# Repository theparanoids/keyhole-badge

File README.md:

# Paranoids DEFCON Badge
> PCB design and firmware for a badge given out at DEFCON 2022

## Table of Contents

- [Background](#background)
- [Install](#install)
- [Usage](#usage)
- [Contribute](#contribute)
- [License](#license)

## Background

The Paranoids have designed a sound-reactive LED electronic conference badge for DEFCON 2022. This repository contains the PCB design files for the badge and the source code to the firmware that runs on the microcontroller.

This badge is designed around a Nordic [nRF52833](https://www.nordicsemi.com/Products/nRF52833) SoC embedded in a Laird [BL653](https://www.lairdconnect.com/wireless-modules/bluetooth-modules/bluetooth-5-modules/bl653-series-bluetooth-51-802154-nfc-module) module. The badge features wireless connectivity (Bluetooth Low Energy in this firmware implementation), a NFC coil, a microphone, buttons, and LEDs.

The firmware is built using the [nRF Connect SDK](https://www.nordicsemi.com/Products/Development-software/nRF-Connect-SDK) and [Zephyr RTOS](https://zephyrproject.org/). It advertises BLE beacons and listens for beacons coming from neighboring badges, lighting up the LEDs according to the number of badges detected. It also blinks the LEDs either in response to sound or in other patterns, which are unlocked by inputting secret codes using the buttons.

## Install

In order to edit the PCB design files, you will need to install [Kicad](https://www.kicad.org/) version 6 or above. The badge design is located in the `eda/` subdirectory. A pogo pin jig used during manufacturing is located in the `jig/` subdirectory. Opening the `.kicad_pro` project file should automatically load both the schematic and PCB design.

If you only want to view the schematic or the final board layout, PDFs of the final version are located in [final-artefacts](final-artefacts).

In order to compile the firmware, you will need to install the [Nordic nRF Connect SDK](https://www.nordicsemi.com/Products/Development-software/nrf-connect-sdk) v1.9.0. This can be installed according to the official instructions. If you are using nRF Connect for Desktop and the Toolchain Manager, select "Open Terminal" from the arrow dropdown after installing the SDK. From this terminal, the firmware can be built using the following command:

```bash
cd fw/
west build
```

The output will be located in `fw/build/zephyr/zephyr.elf`.

There are miscellaneous scripts written in Python that were used during testing and development. These require Python3, pySerial, NumPy, and scikit-image. These can be installed via pip using the following commands:

```bash
# Create a new Python virtual environment
python3 -m venv venv
# Activate the virtual environment
source venv/bin/activate
# Install libraries
pip install pyserial numpy scikit-image
```

LED positions were computed using [SolveSpace](https://solvespace.com/). This is saved in the [notes.slvs](eda/notes.slvs) file.

## Usage

The Paranoids badge does not contain any kind of bootloader or firmware update functionality, so installing new firmware requires connecting to SWD (Serial Wire Debug) test pads on the back of the badge. This can be done either with a temporary jig or by soldering wires or pin headers. The test points are labeled on the [backside fabrication drawing](final-artefacts/badge/pdf/badge_eda-B_Fab.pdf). Connections that are required are as follows:

* `TP3 / +V` -- Microcontroller supply voltage. This may be labeled as "VCC" or "Vtarget" or similar. Corresponds to pin 1 of the ARM 10-pin connector. **Caution**: This pin is intended to be used as a voltage reference and not as a means to power the badge. Although powering the badge from this test point does work, doing so will bypass the reverse polarity protection circuitry. There is also no protection against back-powering the battery, which can result in a dangerous condition. If power is supplied using this test point, ensure that connections are correct and that batteries are not installed. Nominal voltage 3 V.
* `TP9 / GND` -- Ground reference. Corresponds to pins 3/5/9 of the ARM 10-pin connector.
* `TP5 / SWDCLK` -- SWD clock pin. Corresponds to pin 4 of the ARM 10-pin connector.
* `TP6 / SWDIO` -- SWD data pin. Corresponds to pin 2 of the ARM 10-pin connector.
* `TP4 / ~RST` (optional) -- reset pin (active low). Corresponds to pin 10 of the ARM 10-pin connector. Not required in most cases as reset can be triggered over SWD.
* `TP7 / DBGTX` (optional) -- debug serial port, output from the board. In this firmware, this is configured with a 115200 baud 8n1 serial port for printing debug messages.
* `TP8 / DBGRX` (optional) -- debug serial port, input into the board. In this firmware, this is technically configured as part of the debug console, but input is never read.

All signals are referenced to the voltage on `TP3`.

Programming new firmware requires an external ARM SWD debug probe, such as a [Black Magic Probe](https://1bitsquared.com/products/black-magic-probe) or a [J-Link](https://www.segger.com/products/debug-probes/j-link/). It is also possible to [use a Raspberry Pi](https://learn.adafruit.com/programming-microcontrollers-using-openocd-on-raspberry-pi) or any other compatible debug adapter.

Example commands for programming using a Black Magic Probe:

```
$ arm-none-eabi-gdb build/zephyr/zephyr.elf
(gdb) target extended-remote /dev/cu.usbmodemXXXXXXXX
(gdb) monitor swdp_scan
(gdb) attach 1
(gdb) load
```

### Firmware debugging features

The badge connects the USB pins of the nRF52 chip to a USB micro-B connector on the bottom of the board. In this firmware, this is configured as a CDC-ACM serial port featuring a debug console (different from the one on the test points). Typing `help` will show a list of debug commands.

This USB debug console allows for capturing sound onto a connected computer. To capture sound, send the command `debug sound on`. The badge will then continuously output a stream of audio samples in signed 16-bit little endian format at 16 kHz with no framing. The [test_sound.py](fw/src/test_sound.py) script demonstrates capturing approximately 10 seconds of audio via this mechanism and writing it to a raw file which can be opened in tools such as [Audacity](https://www.audacityteam.org/).

If the flash memory of the nRF52 is blank, the firmware will start in factory test mode. Completion of factory testing is stored in flash memory, so none of the badges given out at DEFCON will start in test mode. As long as the Zephyr NVS data at the end of flash memory is not erased when programming new firmware, the badge will not enter test mode again. Test mode can be either re-entered after completion or forcefully bypassed without completing it by using the USB debug console. The factory test procedure goes through the following phases:

1. Both eyes should be red. The edge LEDs should have a pattern of three lit LEDs animating and moving around in a loop. The other LEDs on the edge should be off. One LED should be blue, the next should be green, and the final lit LED should be red. The primary purpose of this test phase is to ensure that there are no breaks in the LED chain. To proceed to the next phase, press button SW1.
2. Both eyes should be green. One LED on the edge, immediately below the eyes, should be white. All other LEDs on the edge should be off. To proceed to the next phase, press button SW2.
3. Both eyes should be blue. Two LEDs on the edge, immediately below the eyes, should be white. All other LEDs on the edge should be off. To proceed to the next phase, press button SW3.
4. Both eyes should be white. Three LEDs on the edge, immediately below the eyes, should be white. All other LEDs on the edge should be off. To proceed to the next phase, press button SW4.
5. Both eyes should be white. All LEDs on the edge should be white. At this point in the test procedure, the edge LEDs, all three primary colors of the eye LEDs, and all buttons will have been tested. This phase with all LEDs lit also serves as a brief test of maximum current draw in order to try to catch obvious issues with the 5 V SMPS. To proceed to the next phase (finishing and exiting test mode), play a 440 Hz tone. This tests the microphone.

## Contribute

Please refer to [the contributing.md file](Contributing.md) for information about how to get involved.

## Maintainers
- R: rou@yahooinc.com

## License
- This project is licensed under the terms of the [Apache 2.0](LICENSE-Apache-2.0) open source license. Please refer to [LICENSE](LICENSE) for the full terms.

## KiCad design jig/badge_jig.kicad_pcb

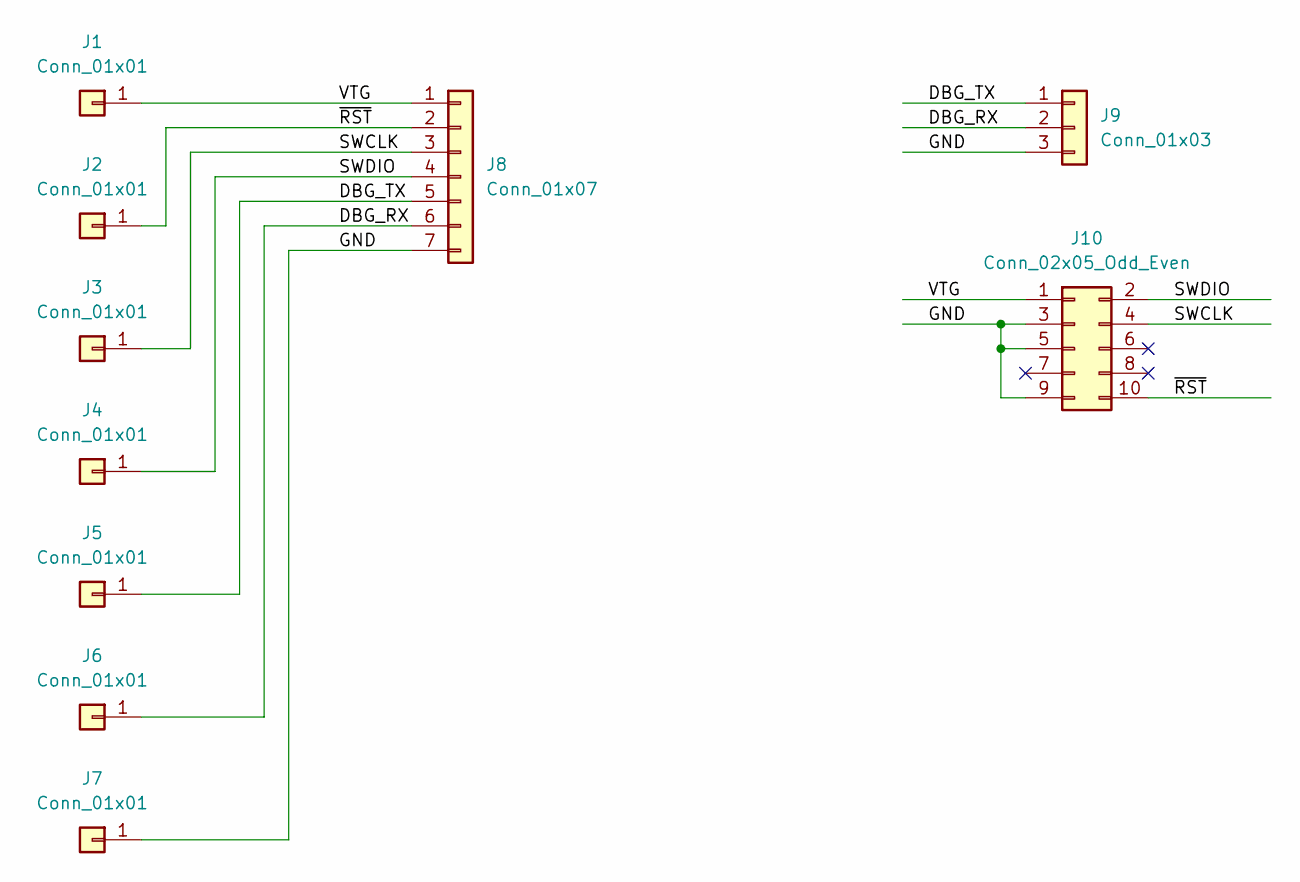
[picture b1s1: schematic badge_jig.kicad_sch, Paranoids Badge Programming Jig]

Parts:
J1, J2, J3, J4, J5, J6, J7: Conn_01x01; pogopin
J8: Conn_01x07; PinHeader_1x07_P2.54mm_Horizontal
J9: Conn_01x03; PinHeader_1x03_P2.54mm_Horizontal
J10: Conn_02x05_Odd_Even; PinHeader_2x05_P2.54mm_Vertical

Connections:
/DBG_RX: J6.1, J8.6, J9.2
/DBG_TX: J5.1, J8.5, J9.1
/GND: J7.1, J8.7, J9.3, J10.3, J10.5, J10.9
/SWCLK: J3.1, J8.3, J10.4
/SWDIO: J4.1, J8.4, J10.2
/VTG: J1.1, J8.1, J10.1
/~RST: J2.1, J8.2, J10.10

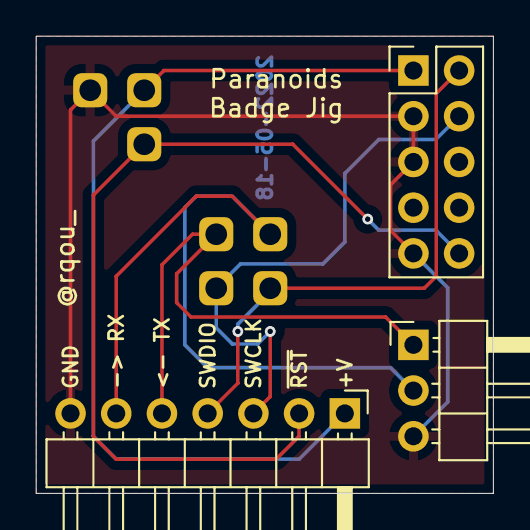
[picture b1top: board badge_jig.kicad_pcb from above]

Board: 2 copper layers, 25.4 x 25.4 mm, 10 parts (0 on the bottom side), 7 nets.

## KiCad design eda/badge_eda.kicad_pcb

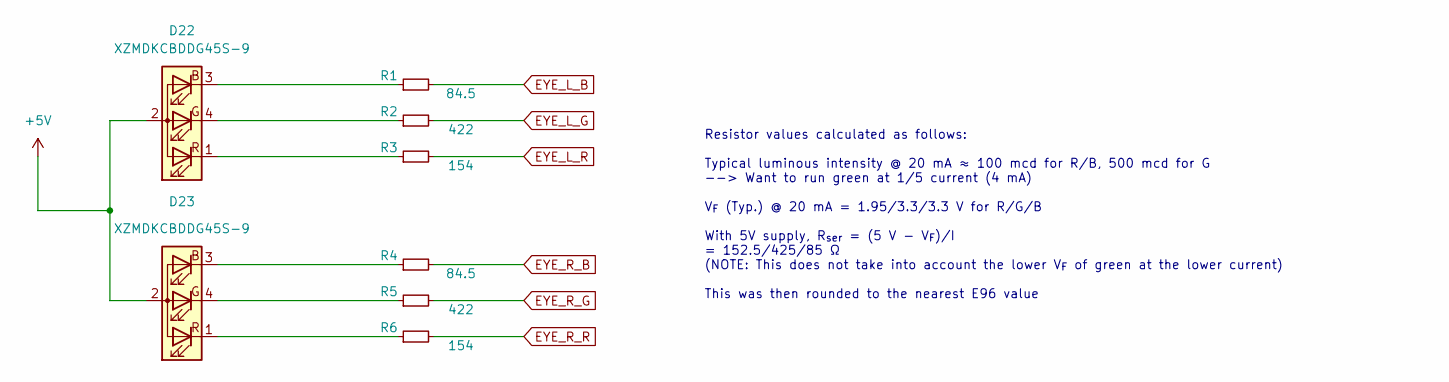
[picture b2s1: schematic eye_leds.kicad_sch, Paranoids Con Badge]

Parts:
D22, D23: XZMDKCBDDG45S-9; LED_SunLed-PLCC4_3.2x2.8mm_CW
R1, R4: 84.5; R_0603_1608Metric
R2, R5: 422; R_0603_1608Metric
R3, R6: 154; R_0603_1608Metric

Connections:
+5V: D22.2 (A), D23.2 (A); also elsewhere on the board
EYE_L_B: R1.2; also elsewhere on the board
EYE_L_G: R2.2; also elsewhere on the board
EYE_L_R: R3.2; also elsewhere on the board
EYE_R_B: R4.2; also elsewhere on the board
EYE_R_G: R5.2; also elsewhere on the board
EYE_R_R: R6.2; also elsewhere on the board
unnamed: D22.1 (RK), R3.1
unnamed: D22.3 (BK), R1.1
unnamed: D22.4 (GK), R2.1
unnamed: D23.1 (RK), R6.1
unnamed: D23.3 (BK), R4.1
unnamed: D23.4 (GK), R5.1

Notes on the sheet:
Resistor values calculated as follows: Typical luminous intensity @ 20 mA ≈ 100 mcd for R/B, 500 mcd for G --> Want to run green at 1/5 current (4 mA) V_{F} (Typ.) @ 20 mA = 1.95/3.3/3.3 V for R/G/B With 5V supply, R_{ser} = (5 V - V_{F})/I = 152.5/425/85 Ω (NOTE: This does not take into account th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

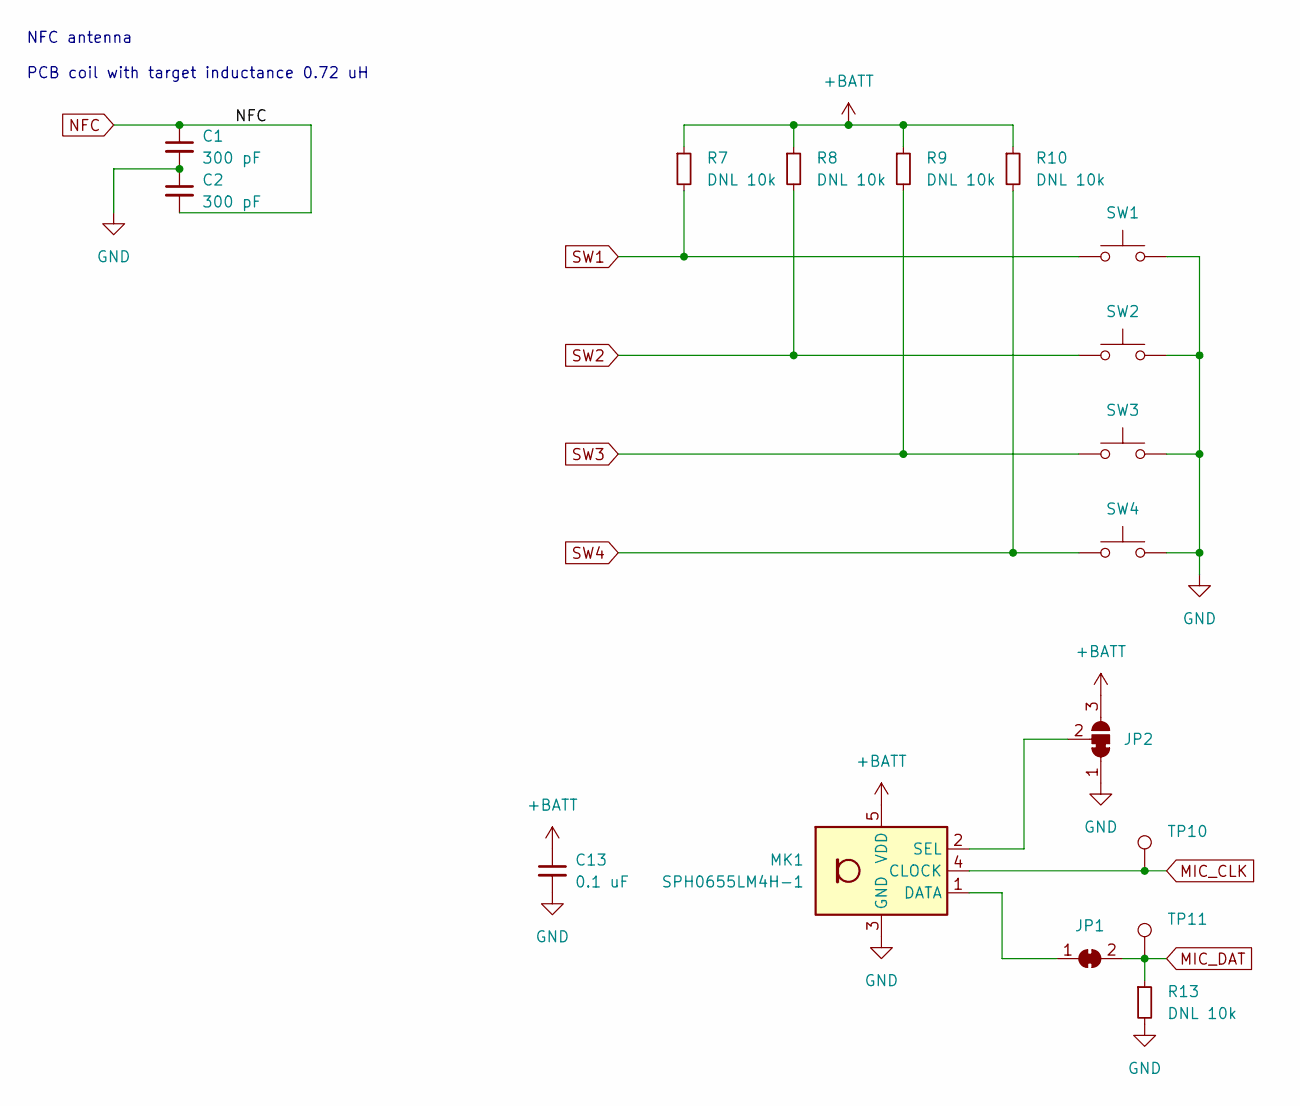
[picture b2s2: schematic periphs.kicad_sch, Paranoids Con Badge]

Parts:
C1, C2: 300 pF; C_0603_1608Metric
C13: 0.1 uF; C_0603_1608Metric
JP1: SolderJumper_2_Bridged; SolderJumper-2_P1.3mm_Bridged_RoundedPad1.0x1.5mm
JP2: SolderJumper_3_Bridged12; SolderJumper-3_P1.3mm_Bridged12_RoundedPad1.0x1.5mm
MK1: SPH0655LM4H-1; Knowles_LGA-5_3.5x2.65mm
R7, R8, R9, R10, R13: DNL 10k; R_0603_1608Metric
SW1, SW2, SW3, SW4: SW_Push; FIXED_SW_Push_1P1T_NO_6x6mm_H9.5mm
TP10, TP11: TestPoint; TestPoint_Pad_1.0x1.0mm

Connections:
+BATT: C13.1, JP2.3 (B), MK1.5 (VDD), R7.1, R8.1, R9.1, R10.1; also elsewhere on the board
GND: C1.2, C2.1, C13.2, JP2.1 (A), MK1.3 (GND), R13.2, SW1.2, SW2.2, SW3.2, SW4.2; also elsewhere on the board
MIC_CLK: MK1.4 (CLOCK), TP10.1; also elsewhere on the board
MIC_DAT: JP1.2 (B), R13.1, TP11.1; also elsewhere on the board
NFC: C1.1, C2.2; also elsewhere on the board
unnamed: JP1.1 (A), MK1.1 (DATA)
unnamed: JP2.2 (C), MK1.2 (SEL)
SW1: R7.2, SW1.1; also elsewhere on the board
SW2: R8.2, SW2.1; also elsewhere on the board
SW3: R9.2, SW3.1; also elsewhere on the board
SW4: R10.2, SW4.1; also elsewhere on the board

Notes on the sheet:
NFC antenna PCB coil with target inductance 0.72 uH

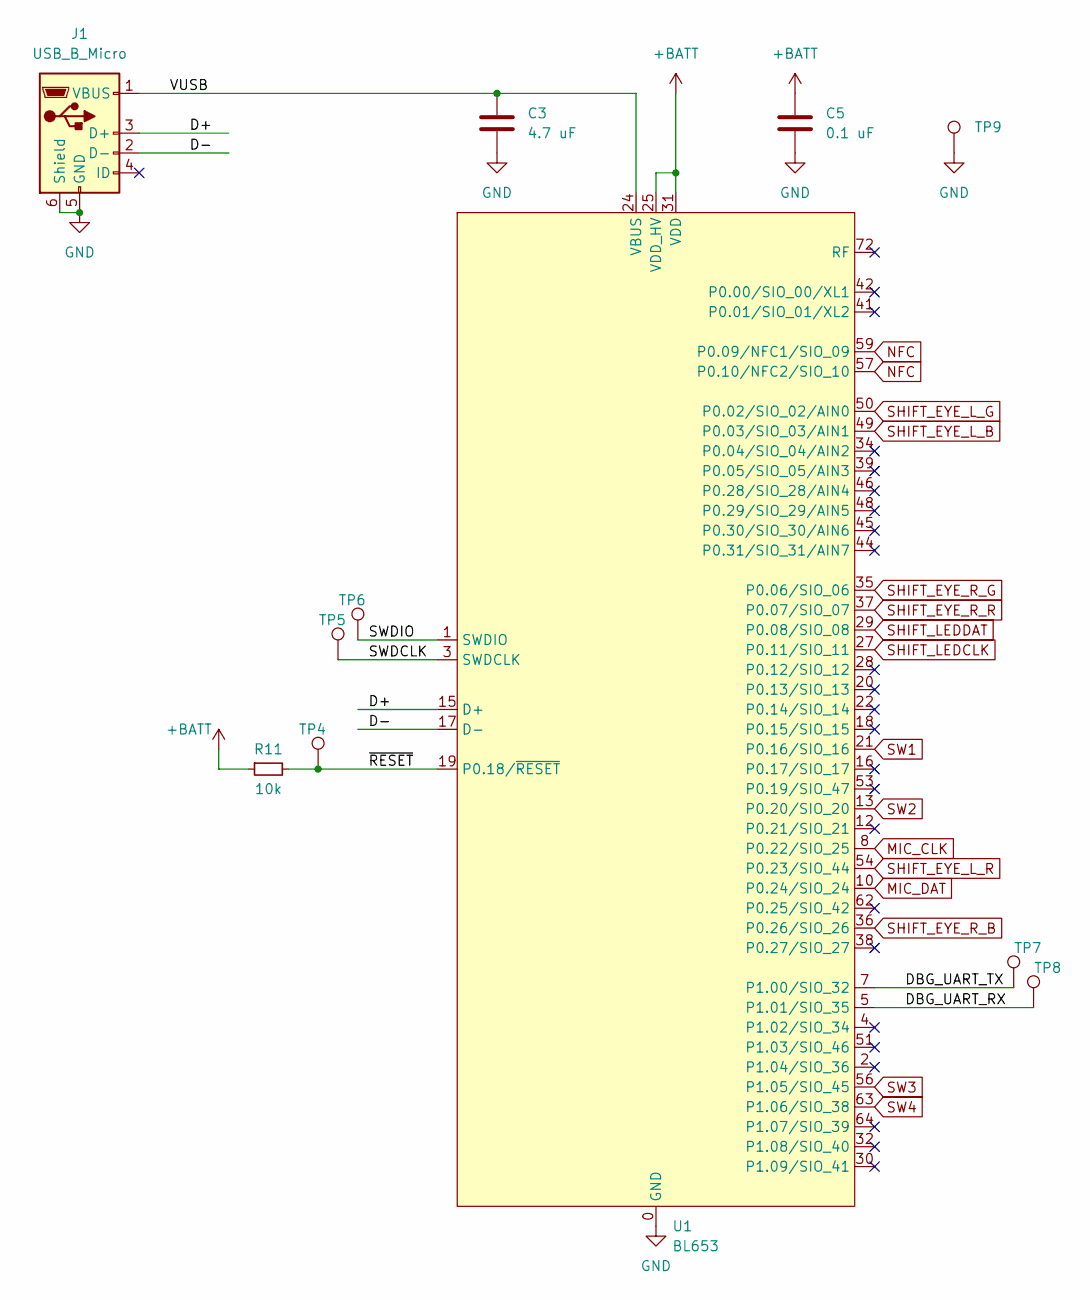
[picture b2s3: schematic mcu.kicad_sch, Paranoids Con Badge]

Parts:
C3: 4.7 uF; C_1206_3216Metric
C5: 0.1 uF; C_0603_1608Metric
J1: USB_B_Micro; USB_Micro-B_Amphenol_10118192-0001LF_Horizontal
R11: 10k; R_0603_1608Metric
TP4, TP5, TP6, TP7, TP8, TP9: TestPoint; TestPoint_Pad_2.0x2.0mm
U1: BL653

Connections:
+BATT: C5.1, R11.1, U1.25 (VDD_HV), U1.31 (VDD); also elsewhere on the board
/MCU/D+: J1.3 (D+), U1.15 (D+)
/MCU/D-: J1.2 (D-), U1.17 (D-)
/MCU/DBG_UART_RX: TP8.1, U1.5 (P1.01/SIO_35)
/MCU/DBG_UART_TX: TP7.1, U1.7 (P1.00/SIO_32)
/MCU/SWDCLK: TP5.1, U1.3 (SWDCLK)
/MCU/SWDIO: TP6.1, U1.1 (SWDIO)
/MCU/VUSB: C3.1, J1.1 (VBUS), U1.24 (VBUS)
/MCU/~RESET: R11.2, TP4.1, U1.19 (P0.18/~RESET)
GND: C3.2, C5.2, J1.5 (GND), J1.6 (Shield), TP9.1, U1.0 (GND), U1.23 (GND), U1.26 (GND), U1.33 (GND), U1.40 (GND), U1.43 (GND), U1.47 (GND), U1.52 (GND), U1.55 (GND), U1.58 (GND), U1.65 (GND), U1.66 (GND), U1.67 (GND), U1.68 (GND), U1.69 (GND), U1.70 (GND), U1.71 (GND); also elsewhere on the board
MIC_CLK: U1.8 (P0.22/SIO_25); also elsewhere on the board
MIC_DAT: U1.10 (P0.24/SIO_24); also elsewhere on the board
NFC: U1.57 (P0.10/NFC2/SIO_10), U1.59 (P0.09/NFC1/SIO_09); also elsewhere on the board
SHIFT_EYE_L_B: U1.49 (P0.03/SIO_03/AIN1); also elsewhere on the board
SHIFT_EYE_L_G: U1.50 (P0.02/SIO_02/AIN0); also elsewhere on the board
SHIFT_EYE_L_R: U1.54 (P0.23/SIO_44); also elsewhere on the board
SHIFT_EYE_R_B: U1.36 (P0.26/SIO_26); also elsewhere on the board
SHIFT_EYE_R_G: U1.35 (P0.06/SIO_06); also elsewhere on the board
SHIFT_EYE_R_R: U1.37 (P0.07/SIO_07); also elsewhere on the board
SHIFT_LEDCLK: U1.27 (P0.11/SIO_11); also elsewhere on the board
SHIFT_LEDDAT: U1.29 (P0.08/SIO_08); also elsewhere on the board
SW1: U1.21 (P0.16/SIO_16); also elsewhere on the board
SW2: U1.13 (P0.20/SIO_20); also elsewhere on the board
SW3: U1.56 (P1.05/SIO_45); also elsewhere on the board
SW4: U1.63 (P1.06/SIO_38); also elsewhere on the board

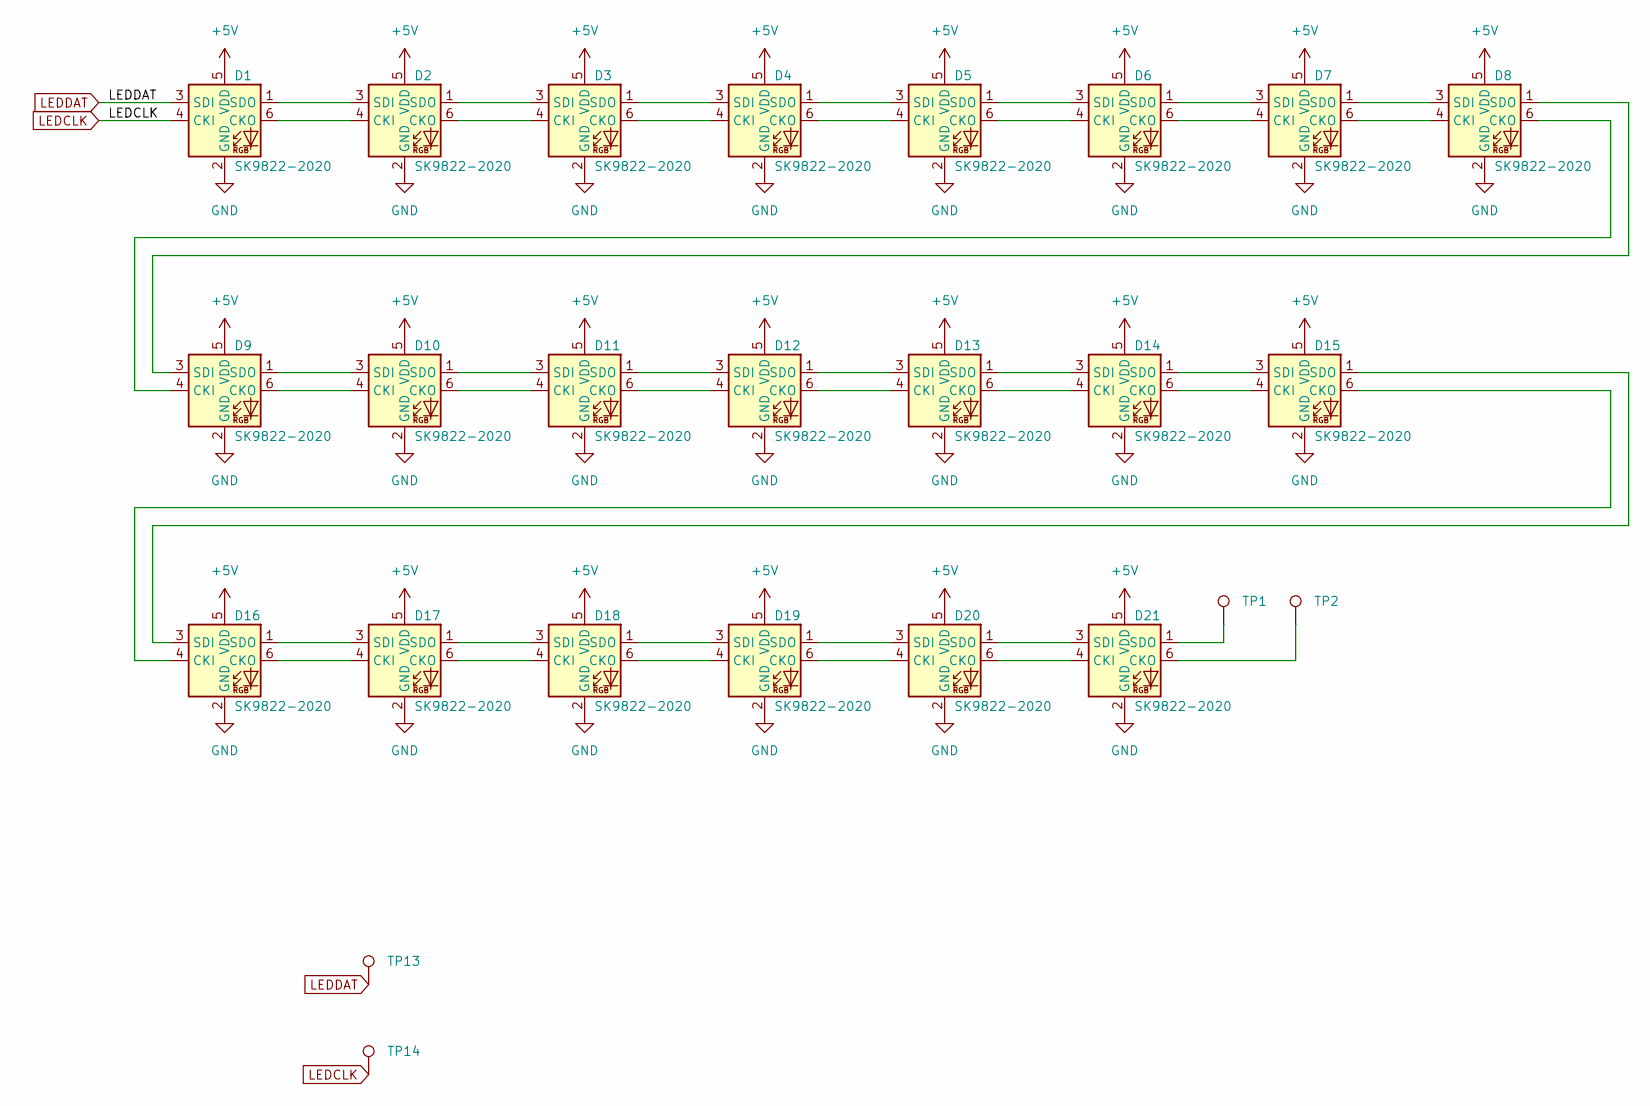
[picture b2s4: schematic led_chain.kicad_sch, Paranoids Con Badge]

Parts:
D1, D2, D3, D4, D5, D6, D7, D8, D9, D10, D11, D12, D13, D14, D15, D16, D17, D18, D19, D20, D21: SK9822-2020; LED-SK9822-2020
TP1, TP2, TP13, TP14: TestPoint; TestPoint_Pad_1.0x1.0mm

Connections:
+5V: D1.5 (VDD), D2.5 (VDD), D3.5 (VDD), D4.5 (VDD), D5.5 (VDD), D6.5 (VDD), D7.5 (VDD), D8.5 (VDD), D9.5 (VDD), D10.5 (VDD), D11.5 (VDD), D12.5 (VDD), D13.5 (VDD), D14.5 (VDD), D15.5 (VDD), D16.5 (VDD), D17.5 (VDD), D18.5 (VDD), D19.5 (VDD), D20.5 (VDD), D21.5 (VDD); also elsewhere on the board
GND: D1.2 (GND), D2.2 (GND), D3.2 (GND), D4.2 (GND), D5.2 (GND), D6.2 (GND), D7.2 (GND), D8.2 (GND), D9.2 (GND), D10.2 (GND), D11.2 (GND), D12.2 (GND), D13.2 (GND), D14.2 (GND), D15.2 (GND), D16.2 (GND), D17.2 (GND), D18.2 (GND), D19.2 (GND), D20.2 (GND), D21.2 (GND); also elsewhere on the board
LEDCLK: D1.4 (CKI), TP14.1; also elsewhere on the board
LEDDAT: D1.3 (SDI), TP13.1; also elsewhere on the board
unnamed: D1.1 (SDO), D2.3 (SDI)
unnamed: D1.6 (CKO), D2.4 (CKI)
unnamed: D2.1 (SDO), D3.3 (SDI)
unnamed: D2.6 (CKO), D3.4 (CKI)
unnamed: D3.1 (SDO), D4.3 (SDI)
unnamed: D3.6 (CKO), D4.4 (CKI)
unnamed: D4.1 (SDO), D5.3 (SDI)
unnamed: D4.6 (CKO), D5.4 (CKI)
unnamed: D5.1 (SDO), D6.3 (SDI)
unnamed: D5.6 (CKO), D6.4 (CKI)
unnamed: D6.1 (SDO), D7.3 (SDI)
unnamed: D6.6 (CKO), D7.4 (CKI)
unnamed: D7.1 (SDO), D8.3 (SDI)
unnamed: D7.6 (CKO), D8.4 (CKI)
unnamed: D8.1 (SDO), D9.3 (SDI)
unnamed: D8.6 (CKO), D9.4 (CKI)
unnamed: D10.1 (SDO), D11.3 (SDI)
unnamed: D9.1 (SDO), D10.3 (SDI)
unnamed: D9.6 (CKO), D10.4 (CKI)
unnamed: D10.6 (CKO), D11.4 (CKI)
unnamed: D11.1 (SDO), D12.3 (SDI)
unnamed: D11.6 (CKO), D12.4 (CKI)
unnamed: D12.1 (SDO), D13.3 (SDI)
unnamed: D12.6 (CKO), D13.4 (CKI)
unnamed: D13.1 (SDO), D14.3 (SDI)
unnamed: D13.6 (CKO), D14.4 (CKI)
unnamed: D14.1 (SDO), D15.3 (SDI)
unnamed: D14.6 (CKO), D15.4 (CKI)
unnamed: D15.1 (SDO), D16.3 (SDI)
unnamed: D15.6 (CKO), D16.4 (CKI)
unnamed: D16.1 (SDO), D17.3 (SDI)
unnamed: D16.6 (CKO), D17.4 (CKI)
unnamed: D17.1 (SDO), D18.3 (SDI)
unnamed: D17.6 (CKO), D18.4 (CKI)
unnamed: D18.1 (SDO), D19.3 (SDI)
unnamed: D18.6 (CKO), D19.4 (CKI)
unnamed: D19.1 (SDO), D20.3 (SDI)
unnamed: D19.6 (CKO), D20.4 (CKI)
unnamed: D20.1 (SDO), D21.3 (SDI)
unnamed: D20.6 (CKO), D21.4 (CKI)
unnamed: D21.1 (SDO), TP1.1
unnamed: D21.6 (CKO), TP2.1

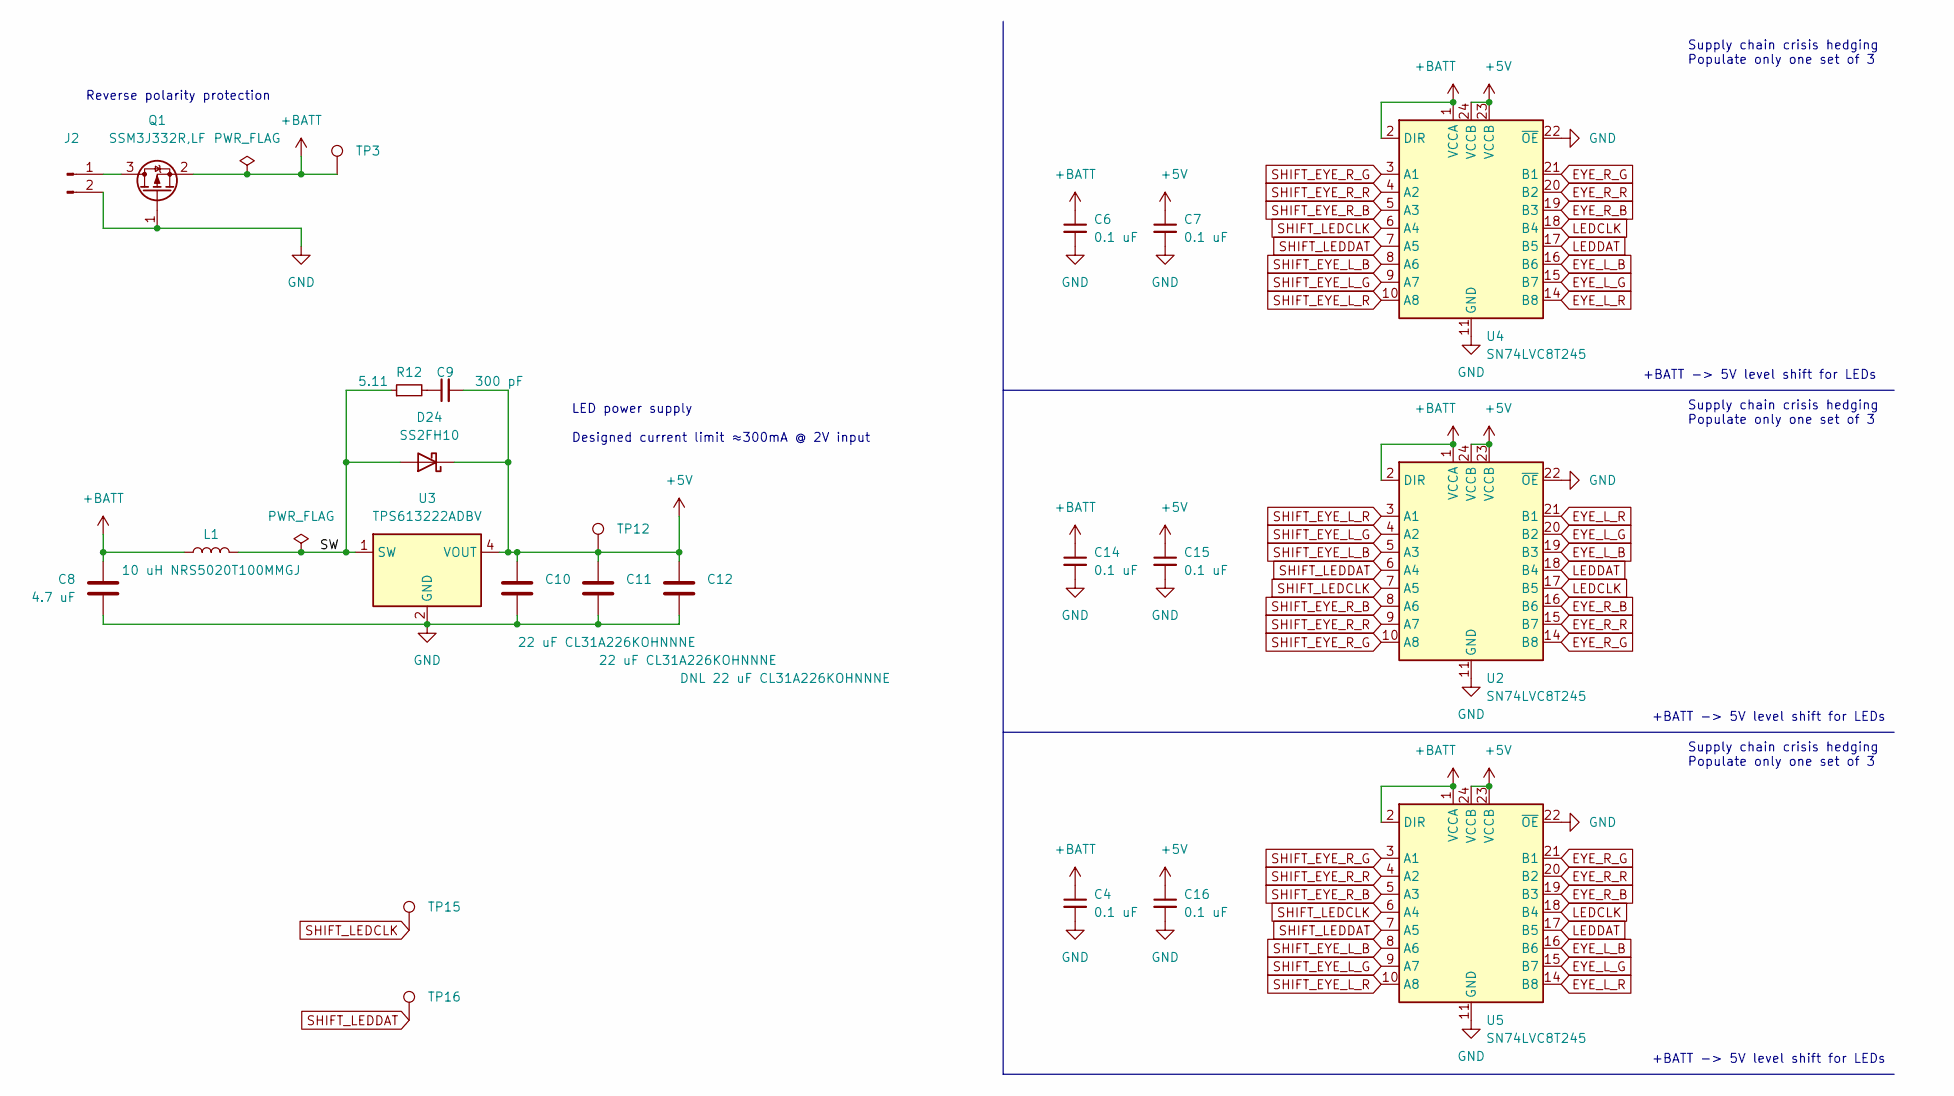
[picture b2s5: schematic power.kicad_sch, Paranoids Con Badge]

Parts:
C4, C6, C7, C14, C15, C16: 0.1 uF; C_0603_1608Metric
C8: 4.7 uF; C_1206_3216Metric
C9: 300 pF; C_0603_1608Metric
C10, C11: 22 uF CL31A226KOHNNNE; C_1206_3216Metric
C12: DNL 22 uF CL31A226KOHNNNE; C_1206_3216Metric
D24: SS2FH10; D_SMF
J2: Conn_01x02_Male; BATTERY_PADS
L1: 10 uH NRS5020T100MMGJ; L_Taiyo-Yuden_NR-50xx
Q1: SSM3J332R,LF; SOT-23
R12: 5.11; R_0603_1608Metric
TP3: TestPoint; TestPoint_Pad_2.0x2.0mm
TP12, TP15, TP16: TestPoint; TestPoint_Pad_1.0x1.0mm
U2: SN74LVC8T245; SupplyChainFML-DB_DBQ_PW-24
U3: TPS613222ADBV; SOT-23-5
U4: SN74LVC8T245; SupplyChainFML-SO_SOIC-24
U5: SN74LVC8T245; TSSOP-24_4.4x5mm_P0.4mm

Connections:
+5V: C7.1, C9.2, C10.1, C11.1, C12.1, C15.1, C16.1, D24.1 (K), TP12.1, U2.23 (VCCB), U2.24 (VCCB), U3.3 (NC), U3.4 (VOUT), U4.23 (VCCB), U4.24 (VCCB), U5.23 (VCCB), U5.24 (VCCB); also elsewhere on the board
+BATT: C4.1, C6.1, C8.2, C14.1, L1.1, Q1.2 (S), TP3.1, U2.1 (VCCA), U2.2 (DIR), U4.1 (VCCA), U4.2 (DIR), U5.1 (VCCA), U5.2 (DIR); also elsewhere on the board
/Power Supplies/SW: D24.2 (A), L1.2, R12.1, U3.1 (SW)
EYE_L_B: U2.19 (B3), U4.16 (B6), U5.16 (B6); also elsewhere on the board
EYE_L_G: U2.20 (B2), U4.15 (B7), U5.15 (B7); also elsewhere on the board
EYE_L_R: U2.21 (B1), U4.14 (B8), U5.14 (B8); also elsewhere on the board
EYE_R_B: U2.16 (B6), U4.19 (B3), U5.19 (B3); also elsewhere on the board
EYE_R_G: U2.14 (B8), U4.21 (B1), U5.21 (B1); also elsewhere on the board
EYE_R_R: U2.15 (B7), U4.20 (B2), U5.20 (B2); also elsewhere on the board
GND: C4.2, C6.2, C7.2, C8.1, C10.2, C11.2, C12.2, C14.2, C15.2, C16.2, J2.2, Q1.1 (G), U2.11 (GND), U2.12 (GND), U2.13 (GND), U2.22 (~OE), U3.2 (GND), U3.5 (NC), U4.11 (GND), U4.12 (GND), U4.13 (GND), U4.22 (~OE), U5.11 (GND), U5.12 (GND), U5.13 (GND), U5.22 (~OE); also elsewhere on the board
LEDCLK: U2.17 (B5), U4.18 (B4), U5.18 (B4); also elsewhere on the board
LEDDAT: U2.18 (B4), U4.17 (B5), U5.17 (B5); also elsewhere on the board
unnamed: C9.1, R12.2
unnamed: J2.1, Q1.3 (D)
SHIFT_EYE_L_B: U2.5 (A3), U4.8 (A6), U5.8 (A6); also elsewhere on the board
SHIFT_EYE_L_G: U2.4 (A2), U4.9 (A7), U5.9 (A7); also elsewhere on the board
SHIFT_EYE_L_R: U2.3 (A1), U4.10 (A8), U5.10 (A8); also elsewhere on the board
SHIFT_EYE_R_B: U2.8 (A6), U4.5 (A3), U5.5 (A3); also elsewhere on the board
SHIFT_EYE_R_G: U2.10 (A8), U4.3 (A1), U5.3 (A1); also elsewhere on the board
SHIFT_EYE_R_R: U2.9 (A7), U4.4 (A2), U5.4 (A2); also elsewhere on the board
SHIFT_LEDCLK: TP15.1, U2.7 (A5), U4.6 (A4), U5.6 (A4); also elsewhere on the board
SHIFT_LEDDAT: TP16.1, U2.6 (A4), U4.7 (A5), U5.7 (A5); also elsewhere on the board

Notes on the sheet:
+BATT -> 5V level shift for LEDs
Reverse polarity protection
LED power supply Designed current limit ≈300mA @ 2V input
Supply chain crisis hedging Populate only one set of 3

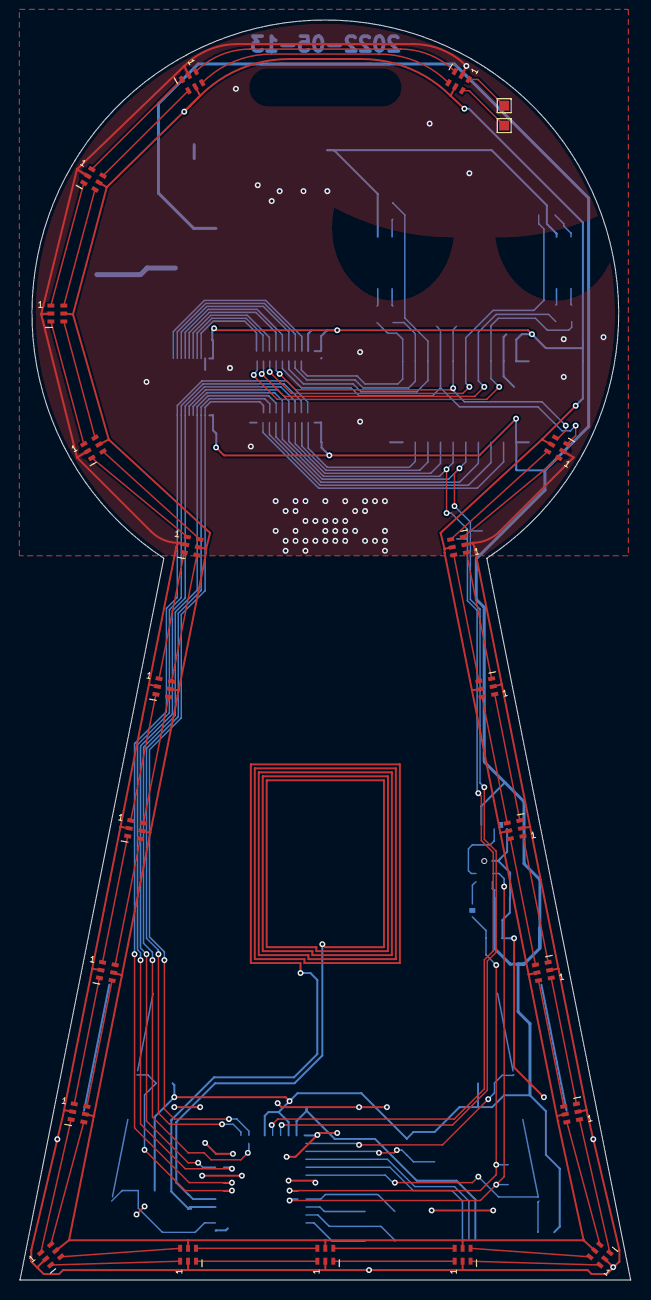
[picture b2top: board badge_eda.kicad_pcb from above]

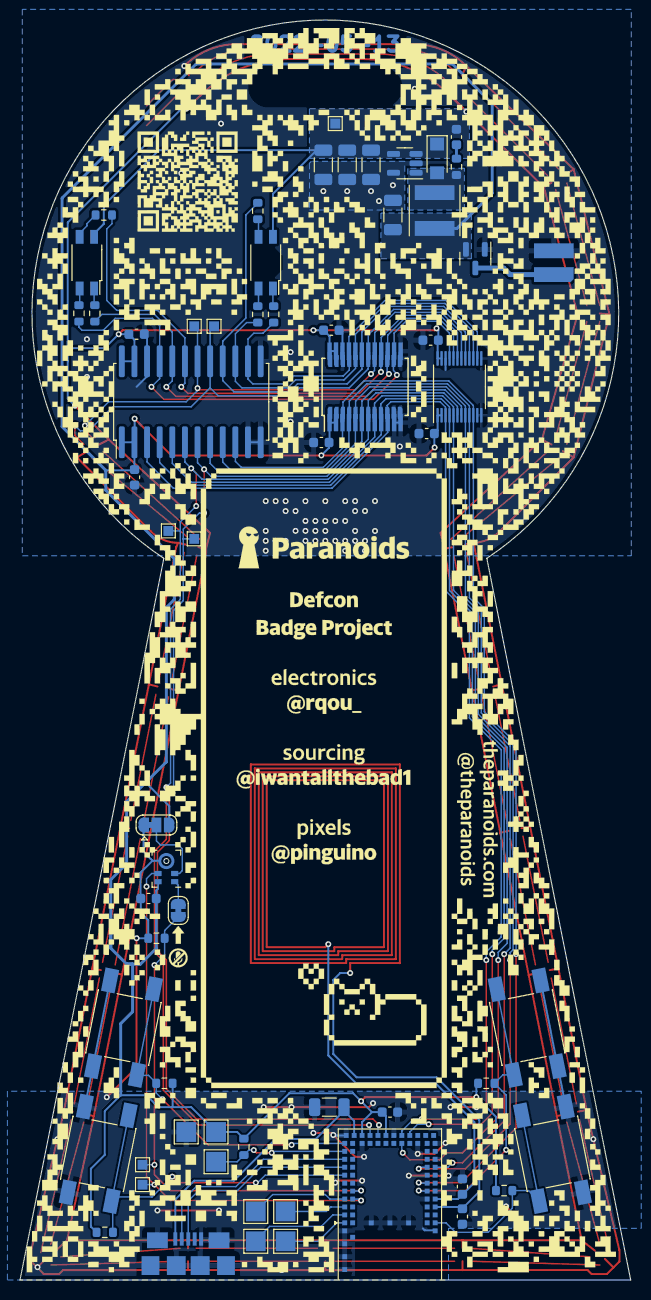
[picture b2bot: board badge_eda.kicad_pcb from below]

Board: 2 copper layers, 61.5 x 126.8 mm, 87 parts (63 on the bottom side), 87 nets.

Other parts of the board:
Ref**: Val**; badge-eyes
Ref**#2: Val**; background8_text_v7b

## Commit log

2022-07-15 sekrit

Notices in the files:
eda/badge_eda.kicad_pcb:
See LICENSE file in project root for terms.
Copyright Yahoo, Licensed under the terms of the Apache-2.0 license.
